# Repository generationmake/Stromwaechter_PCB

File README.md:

# Stromwaechter
current and voltage monitor and power distribution for 12 V battery systems.

Stromwaechter on the left connected via WiFi to a Raspberry Pi 3 running OpenHAB on the right.

## Introduction

Stromwaechter is a pcb intended for power distribution and monitoring in remote hamradio stations. It has four channels with a dedicated fuse and a switch for each channel. On each channel current and voltage is monitored. The data is collected by an ESP8266 and transmitted via WiFi using the MQTT protocol. The board is intended to be used with a pc running OpenHAB for visualisation and logging but it may also be connected to any MQTT server.

## Hardware

The Stromwaechter has 4 output channels. Each channel can be switched by an Infineon ITS4200S. This IC has an internal over current and short circuit protection. Additionally each channel is protected by an ATO blade fuse. Also each channel has an TI INA226 to measure voltage and current on each channel. This allows to measure current in the range of -4.096 A to +4.096 A.

## Limitations

The stromwaechter PCB is intended to monitor current flowing from the bus connector to loads connected on each channel. It is also possible that current flows in the reverse direction from the output to the bus. In this case the internal short circuit and over current protections of the ITS4200S don't work anymore and there is a 600 mV voltage drop across the ITS4200S because of its internal diode.

## License

The hardware is released under CERN OHL v1.2

## Software

You can find the software on github: https://github.com/generationmake/stromwaechter
The software is released under GPL v3

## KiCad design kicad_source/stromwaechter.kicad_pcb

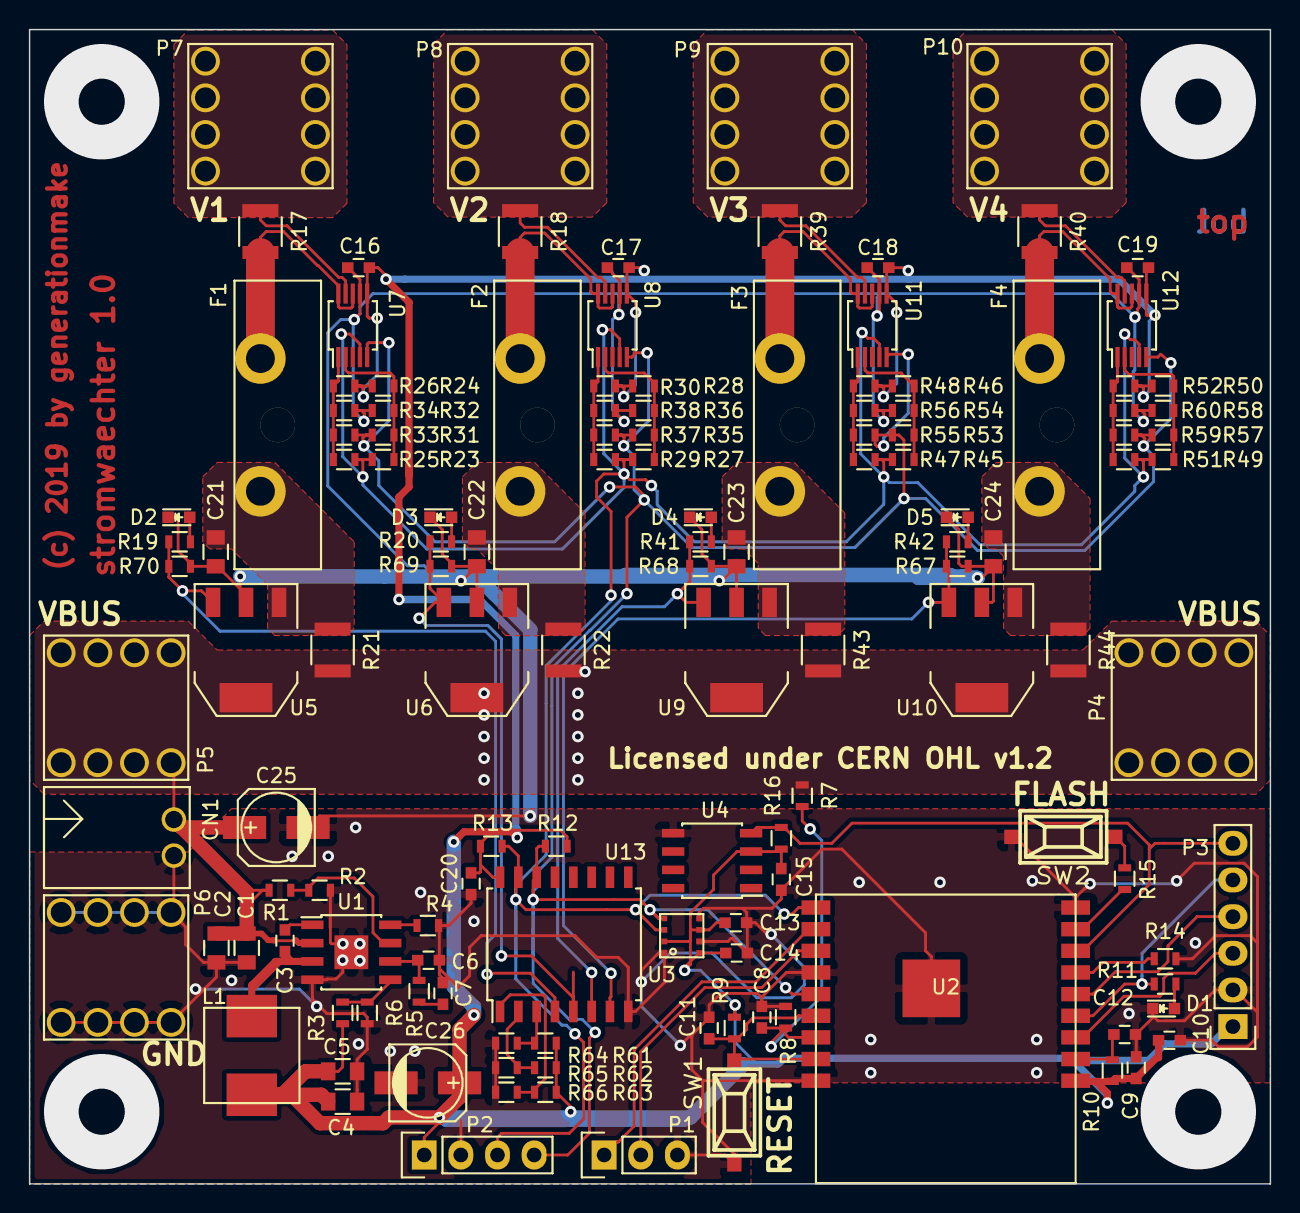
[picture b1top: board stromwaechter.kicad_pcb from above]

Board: 2 copper layers, 86.0 x 80.0 mm, 132 parts (0 on the bottom side), 56 nets.

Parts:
C1, C2, C4, C5, C21, C22, C23, C24: C_0805
C3, C6, C7, C8, C9, C10, C11, C12, C13, C14, C15, C16, C17, C18, C19, C20: C_0603
C25, C26: CP_Small; c_elec_5x5.8
CN1: 691382010002; WR-TBL_691382010002
D1, D2, D3, D4, D5: Led_Small; LED_0603
F1, F2, F3, F4: F_Small; Fuseholder_ATO_Blade_littlefuse_Pudenz_2_Pin
L1: 74437346220; WE-LHMI70xx
P1: CONN_01X03; Pin_Header_Straight_1x03
P2: CONN_01X04; Pin_Header_Straight_1x04
P3: CONN_01X06; Pin_Header_Straight_1x06
P4, P5, P6, P7, P8, P9, P10: CONN_01X01; WP-BUTR_7461084
R1, R2, R3, R4, R5, R6, R7, R8, R9, R10, R11, R12, R13, R14, R15, R16, R19, R20, R23, R24, R25, R26, R27, R28, R29, R30, R31, R32, R33, R34, R35, R36, R37, R38, R41, R42, R45, R46, R47, R48, R49, R50, R51, R52, R53, R54, R55, R56, R57, R58, R59, R60, R61, R62, R63, R64, R65, R66, R67, R68, R69, R70: R_0603
R17, R18, R21, R22, R39, R40, R43, R44: R_1210
SW1, SW2: SW_PUSH; smd_push
U1: TPS54335A; SOIC-8-1EP_3.9x4.9mm_Pitch1.27mm
U2: ESP_WROOM_02; ESP-WROOM-02
U3: BME680
U4: DS18B20; SOIC-8_3.9x4.9mm_Pitch1.27mm
U5, U6, U9, U10: ITS4200S-ME; SOT-223
U7, U8, U11, U12: INA226; MSOP-10_3x3mm_Pitch0.5mm
U13: TCA9534; SOIC-16_7.5x10.3mm_Pitch1.27mm

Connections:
+3V3: C4.1, C5.1, C9.1, C10.1, C13.1, C14.1, C15.1, C16.1, C17.1, C18.1, C19.1, C20.1, C26.1, L1.2, P2.1, P3.1, R3.1, R9.1, R10.1, R12.1, R13.1, R16.1, R24.1, R26.1, R28.1, R30.1, R46.1, R48.1, R50.1, R52.1, R61.2, R62.2, R63.2, U2.1, U3.2, U3.6, U3.8, U4.3, U7.6, U8.6, U11.6, U12.6, U13.16
/1wire: P3.6, R16.2, U2.7, U4.4
/ADC: C8.1, R7.2, R8.1, U2.16
/BOOT: C3.1, U1.1
/COMP: C6.1, R5.1, U1.6
/EN: C12.1, R10.2, U2.2
/FLASH: R15.1, U2.8
/IO13: P3.4, U2.5
/IO14: P3.3, U2.3
/IO15: R14.1, U2.6
/Input/Output/EN0: R19.2, R70.2, U5.3, U13.4
/Input/Output/EN1: R20.2, R69.2, U6.3, U13.5
/Input/Output/EN2: R41.2, R68.2, U9.3, U13.6
/Input/Output/EN3: R42.2, R67.2, U10.3, U13.7
/Input/Output/INA0_A0: R23.1, R24.2, R31.1, R32.2, U7.2
/Input/Output/INA0_A1: R25.1, R26.2, R33.1, R34.2, U7.1
/Input/Output/INA0_F: C21.1, F1.1, R21.1, U5.1
/Input/Output/INA0_VIN: F1.2, R17.2, U7.8, U7.10
/Input/Output/INA1_A0: R27.1, R28.2, R35.1, R36.2, U8.2
/Input/Output/INA1_A1: R29.1, R30.2, R37.1, R38.2, U8.1
/Input/Output/INA1_F: C22.1, F2.1, R22.1, U6.1
/Input/Output/INA1_VIN: F2.2, R18.2, U8.8, U8.10
/Input/Output/INA2_A0: R45.1, R46.2, R53.1, R54.2, U11.2
/Input/Output/INA2_A1: R47.1, R48.2, R55.1, R56.2, U11.1
/Input/Output/INA2_F: C23.1, F3.1, R43.1, U9.1
/Input/Output/INA2_VIN: F3.2, R39.2, U11.8, U11.10
/Input/Output/INA3_A0: R49.1, R50.2, R57.1, R58.2, U12.2
/Input/Output/INA3_A1: R51.1, R52.2, R59.1, R60.2, U12.1
/Input/Output/INA3_F: C24.1, F4.1, R44.1, U10.1
/Input/Output/INA3_VIN: F4.2, R40.2, U12.8, U12.10
/Input/Output/INOUT0: P7.1, R17.1, U7.9
/Input/Output/INOUT1: P8.1, R18.1, U8.9
/Input/Output/INOUT2: P9.1, R39.1, U11.9
/Input/Output/INOUT3: P10.1, R40.1, U12.9
/Input/Output/IO_A0: R63.1, R66.2, U13.1
/Input/Output/IO_A1: R62.1, R65.2, U13.2
/Input/Output/IO_A2: R61.1, R64.2, U13.3
/LED: P3.5, R11.2, U2.4
/PH: C3.2, L1.1, U1.3
/RESET: C11.1, R9.2, SW1.1, U2.15, U2.17
/RT: R4.1, U1.8
/RxD: P1.1, U2.11
/TxD: P1.2, U2.12
/VIN_EN: R1.2, R2.1, U1.7
/VSENSE: R3.2, R6.1, U1.5
GND: C1.2, C2.2, C4.2, C5.2, C6.2, C7.2, C8.2, C9.2, C10.2, C11.2, C12.2, C13.2, C14.2, C15.2, C16.2, C17.2, C18.2, C19.2, C20.2, C21.2, C22.2, C23.2, C24.2, C25.2, C26.2, CN1.2, D1.1, D2.1, D3.1, D4.1, D5.1, P1.3, P2.2, P3.2, P6.1, R2.2, R4.2, R6.2, R8.2, R14.2, R32.1, R34.1, R36.1, R38.1, R54.1, R56.1, R58.1, R60.1, R64.1, R65.1, R66.1, R67.1, R68.1, R69.1, R70.1, SW1.2, SW2.2, U1.4, U1.9, U2.9, U2.13, U2.18, U2.19, U3.1, U3.5, U3.7, U4.5, U5.2, U6.2, U7.7, U8.7, U9.2, U10.2, U11.7, U12.7, U13.8
unnamed: C7.1, R5.2
unnamed: D1.2, R11.1
unnamed: D2.2, R19.1
unnamed: D3.2, R20.1
unnamed: D4.2, R41.1
unnamed: D5.2, R42.1
unnamed: R15.2, SW2.1
SCL: P2.4, R12.2, R31.2, R33.2, R35.2, R37.2, R53.2, R55.2, R57.2, R59.2, U2.14, U3.4, U7.5, U8.5, U11.5, U12.5, U13.14
SDA: P2.3, R13.2, R23.2, R25.2, R27.2, R29.2, R45.2, R47.2, R49.2, R51.2, U2.10, U3.3, U7.4, U8.4, U11.4, U12.4, U13.15
VIN: C1.1, C2.1, C25.1, CN1.1, P4.1, P5.1, R1.1, R7.1, R21.2, R22.2, R43.2, R44.2, U1.2, U5.4, U6.4, U9.4, U10.4

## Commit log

2025-09-01 added files from project
2025-09-01 added image
2025-09-01 fixed readme

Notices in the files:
kicad_source/stromwaechter.kicad_pcb:
This documentation describes Open Hardware and is licensed
under the CERN OHL v. 1.2.
of the CERN OHL v.1.2. (http://ohwr.org/cernohl). This documentation
Licensed under CERN OHL v1.2
(c) 2019 by generationmake
